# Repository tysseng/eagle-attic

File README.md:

# eagle-attic
Old eagle projects

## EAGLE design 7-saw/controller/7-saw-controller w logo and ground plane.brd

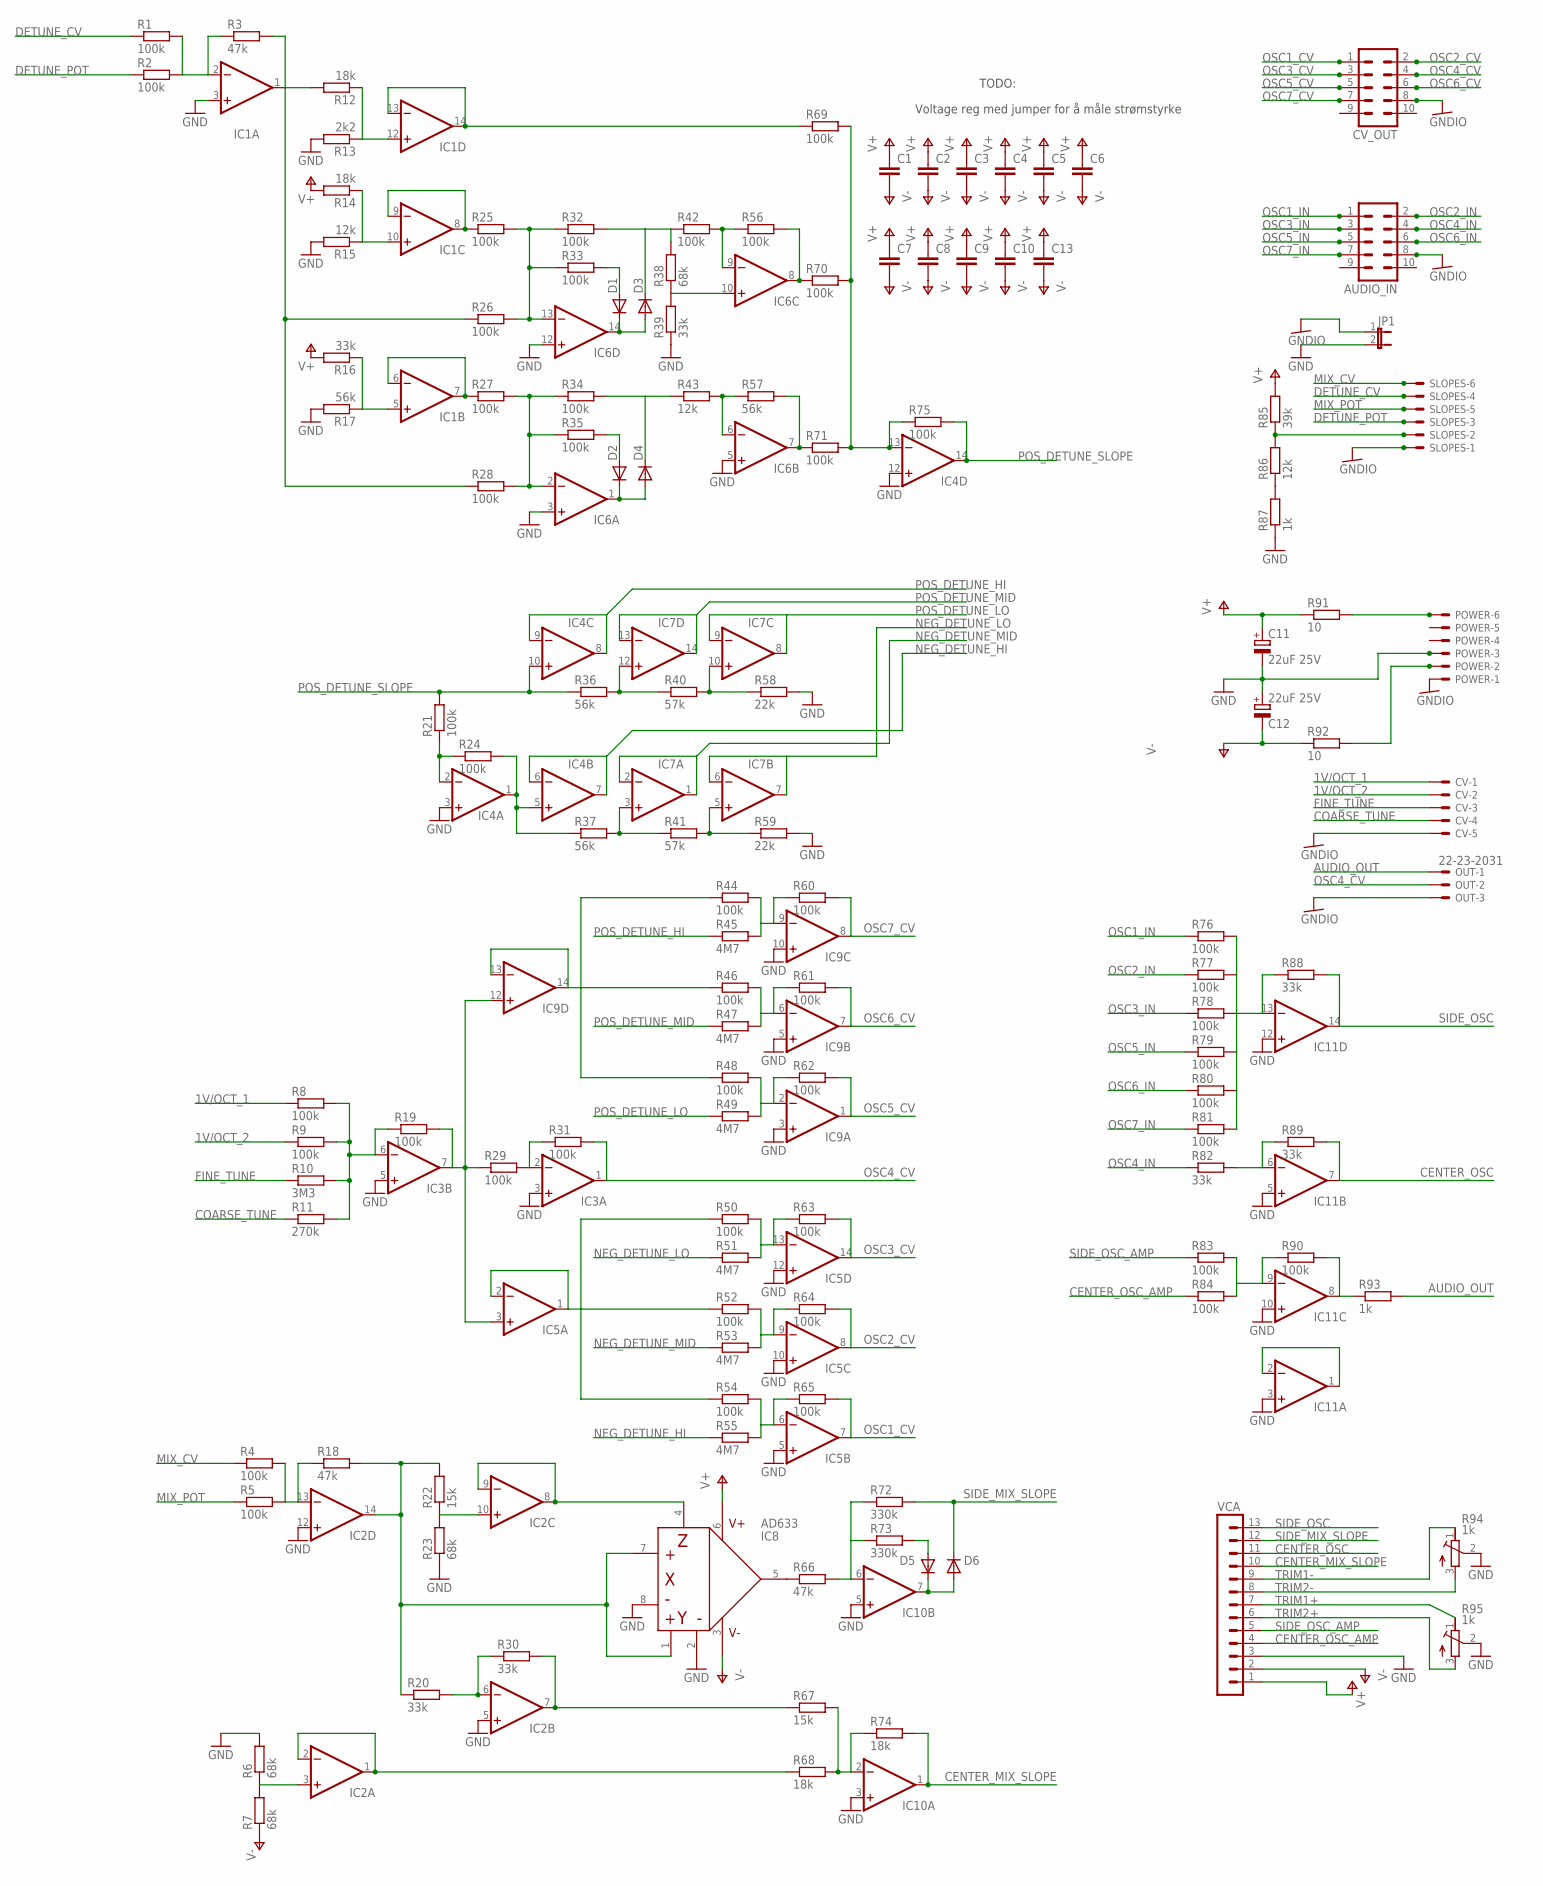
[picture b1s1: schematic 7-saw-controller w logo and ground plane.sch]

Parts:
AUDIO_IN: MA05-2
C1, C2, C3, C4, C5, C6, C7, C8, C9, C10, C13: C-EU025-024X044; C025-024X044
C11, C12: 22uF 25V; E2-5
CV: 22-23-2051
CV_OUT: MA05-2
D1, D2, D3, D4, D5, D6: DIODE-D-5; D-5
IC1, IC2, IC4, IC5, IC6, IC7, IC9, IC11: TL074D; SO14
IC3, IC10: TL072D; SO08
IC8: AD633; SO08
JP1: JP1E; JP1
OUT: 22-23-2031
POWER: 22-23-2061
R1, R2, R4, R5, R8, R9, R19, R21, R24, R25, R26, R27, R28, R29, R31, R32, R33, R34, R35, R42, R44, R46, R48, R50, R52, R54, R56, R60, R61, R62, R63, R64, R65, R69, R70, R71, R75, R76, R77, R78, R79, R80, R81, R83, R84, R90: 100k; 0204/5
R3, R18, R66: 47k; 0204/5
R6, R7, R23, R38: 68k; 0204/5
R10: 3M3; 0204/5
R11: 270k; 0204/5
R12, R14, R68, R74: 18k; 0204/5
R13: 2k2; 0204/5
R15, R43, R86: 12k; 0204/5
R16, R20, R30, R39, R82, R88, R89: 33k; 0204/5
R17, R36, R37, R57: 56k; 0204/5
R22, R67: 15k; 0204/5
R40, R41: 57k; 0204/5
R45, R47, R49, R51, R53, R55: 4M7; 0204/5
R58, R59: 22k; 0204/5
R72, R73: 330k; 0204/5
R85: 39k; 0204/5
R87, R93: 1k; 0204/5
R91, R92: 10; 0204/7
R94, R95: 1k; RTRIMT93YA
SLOPES: 22-23-2061
VCA: MA13-1

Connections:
1V/OCT_1: CV.1, R8.1
1V/OCT_2: CV.2, R9.1
AUDIO_OUT: OUT.1, R93.2
CENTER_MIX_SLOPE: IC10.1 (OUT), R74.2, VCA.10
CENTER_OSC: IC11.7 (OUT), R89.2, VCA.11
CENTER_OSC_AMP: R84.1, VCA.4
COARSE_TUNE: CV.4, R11.1
DETUNE_CV: R1.1, SLOPES.4
DETUNE_MIXED: R12.2, R26.1, R28.1
DETUNE_POT: R2.1, SLOPES.3
FINE_TUNE: CV.3, R10.1
GND: C11.-, C12.+, IC1.3 (+IN), IC2.5 (+IN), IC2.12 (+IN), IC3.3 (+IN), IC3.5 (+IN), IC4.3 (+IN), IC4.12 (+IN), IC5.5 (+IN), IC5.10 (+IN), IC5.12 (+IN), IC6.3 (+IN), IC6.5 (+IN), IC6.12 (+IN), IC8.2, IC8.8, IC9.3 (+IN), IC9.5 (+IN), IC9.10 (+IN), IC10.3 (+IN), IC10.5 (+IN), IC11.3 (+IN), IC11.5 (+IN), IC11.10 (+IN), IC11.12 (+IN), JP1.2, POWER.3, R6.2, R13.2, R15.2, R17.2, R23.1, R39.1, R58.2, R59.2, R87.1, R94.2 (S), R95.2 (S), VCA.3
GNDIO: AUDIO_IN.8, CV.5, CV_OUT.8, JP1.1, OUT.3, POWER.1, SLOPES.1
MIX_CV: R4.1, SLOPES.6
MIX_POT: R5.1, SLOPES.5
unnamed: IC1.12 (+IN), R12.1, R13.1
unnamed: IC1.13 (-IN), IC1.14 (OUT), R69.1
unnamed: IC1.10 (+IN), R14.1, R15.1
unnamed: IC1.8 (OUT), IC1.9 (-IN), R25.1
unnamed: IC6.13 (-IN), R25.2, R26.2, R32.1, R33.1
unnamed: IC6.7 (OUT), R57.2, R71.1
unnamed: IC10.2 (-IN), R67.2, R68.2, R74.1
unnamed: IC3.7 (OUT), IC5.3 (+IN), IC9.12 (+IN), R19.2, R29.1
unnamed: IC4.13 (-IN), R69.2, R70.2, R71.2, R75.1
unnamed: D1.A, R33.2
unnamed: D1.C, D3.A, IC6.14 (OUT)
unnamed: D3.C, R32.2, R38.2, R42.1
unnamed: IC2.14 (OUT), IC8.1, IC8.7, R18.2, R20.1, R22.2
unnamed: IC6.9 (-IN), R42.2, R56.1
unnamed: IC6.10 (+IN), R38.1, R39.2
unnamed: IC6.8 (OUT), R56.2, R70.1
unnamed: IC2.8 (OUT), IC2.9 (-IN), IC8.4
unnamed: IC1.5 (+IN), R16.1, R17.1
unnamed: IC1.6 (-IN), IC1.7 (OUT), R27.1
unnamed: IC2.10 (+IN), R22.1, R23.2
unnamed: IC6.2 (-IN), R27.2, R28.2, R34.1, R35.1
unnamed: D5.A, R73.2
unnamed: IC2.3 (+IN), R6.1, R7.2
unnamed: D2.A, R35.2
unnamed: D2.C, D4.A, IC6.1 (OUT)
unnamed: D4.C, R34.2, R43.1
unnamed: IC6.6 (-IN), R43.2, R57.1
unnamed: D5.C, D6.A, IC10.7 (OUT)
unnamed: IC2.1 (OUT), IC2.2 (-IN), R68.1
unnamed: IC2.6 (-IN), R20.2, R30.1
unnamed: IC2.7 (OUT), R30.2, R67.1
unnamed: IC9.9 (-IN), R44.2, R45.2, R60.1
unnamed: IC5.13 (-IN), R50.2, R51.2, R63.1
unnamed: IC5.9 (-IN), R52.2, R53.2, R64.1
unnamed: IC8.5, R66.1
unnamed: IC5.6 (-IN), R54.2, R55.2, R65.1
unnamed: IC10.6 (-IN), R66.2, R72.1, R73.1
unnamed: IC5.1 (OUT), IC5.2 (-IN), R50.1, R52.1, R54.1
unnamed: IC9.6 (-IN), R46.2, R47.2, R61.1
unnamed: POWER.6, R91.2
unnamed: IC9.13 (-IN), IC9.14 (OUT), R44.1, R46.1, R48.1
unnamed: R85.1, R86.2, SLOPES.2
unnamed: IC9.2 (-IN), R48.2, R49.2, R62.1
unnamed: POWER.2, R92.2
unnamed: IC3.6 (-IN), R8.2, R9.2, R10.2, R11.2, R19.1
unnamed: IC11.13 (-IN), R76.2, R77.2, R78.2, R79.2, R80.2, R81.2, R88.1
unnamed: IC11.6 (-IN), R82.2, R89.1
unnamed: IC11.9 (-IN), R83.2, R84.2, R90.1
unnamed: IC1.1 (OUT), R3.2
unnamed: IC11.8 (OUT), R90.2, R93.1
unnamed: IC2.13 (-IN), R4.2, R5.2, R18.1
unnamed: IC7.12 (+IN), R36.2, R40.1
unnamed: IC7.10 (+IN), R40.2, R58.1
unnamed: IC4.1 (OUT), IC4.5 (+IN), R24.2, R37.1
unnamed: IC1.2 (-IN), R1.2, R2.2, R3.1
unnamed: IC3.2 (-IN), R29.2, R31.1
unnamed: IC7.3 (+IN), R37.2, R41.1
unnamed: IC7.5 (+IN), R41.2, R59.1
unnamed: R86.1, R87.2
unnamed: IC4.2 (-IN), R21.1, R24.1
unnamed: IC11.1 (OUT), IC11.2 (-IN)
NEG_DETUNE_HI: IC4.6 (-IN), IC4.7 (OUT), R55.1
NEG_DETUNE_LO: IC7.6 (-IN), IC7.7 (OUT), R51.1
NEG_DETUNE_MID: IC7.1 (OUT), IC7.2 (-IN), R53.1
OSC1_CV: CV_OUT.1, IC5.7 (OUT), R65.2
OSC1_IN: AUDIO_IN.1, R76.1
OSC2_CV: CV_OUT.2, IC5.8 (OUT), R64.2
OSC2_IN: AUDIO_IN.2, R77.1
OSC3_CV: CV_OUT.3, IC5.14 (OUT), R63.2
OSC3_IN: AUDIO_IN.3, R78.1
OSC4_CV: CV_OUT.4, IC3.1 (OUT), OUT.2, R31.2
OSC4_IN: AUDIO_IN.4, R82.1
OSC5_CV: CV_OUT.5, IC9.1 (OUT), R62.2
OSC5_IN: AUDIO_IN.5, R79.1
OSC6_CV: CV_OUT.6, IC9.7 (OUT), R61.2
OSC6_IN: AUDIO_IN.6, R80.1
OSC7_CV: CV_OUT.7, IC9.8 (OUT), R60.2
OSC7_IN: AUDIO_IN.7, R81.1
POS_DETUNE_HI: IC4.8 (OUT), IC4.9 (-IN), R45.1
POS_DETUNE_LO: IC7.8 (OUT), IC7.9 (-IN), R49.1
POS_DETUNE_MID: IC7.13 (-IN), IC7.14 (OUT), R47.1
POS_DETUNE_SLOPE: IC4.10 (+IN), IC4.14 (OUT), R21.2, R36.1, R75.2
SIDE_MIX_SLOPE: D6.C, R72.2, VCA.12
SIDE_OSC: IC11.14 (OUT), R88.2, VCA.13
SIDE_OSC_AMP: R83.1, VCA.5
TRIM1+: R94.3 (E), VCA.8
TRIM1-: R94.1 (A), VCA.9
TRIM2+: R95.3 (E), VCA.6
TRIM2-: R95.1 (A), VCA.7
V+: C1.1, C2.1, C3.1, C4.1, C5.1, C6.1, C7.1, C8.1, C9.1, C10.1, C11.+, C13.1, IC1.4 (V+), IC2.4 (V+), IC3.8 (V+), IC4.4 (V+), IC5.4 (V+), IC6.4 (V+), IC7.4 (V+), IC8.6, IC9.4 (V+), IC10.8 (V+), IC11.4 (V+), R14.2, R16.2, R85.2, R91.1, VCA.1
V-: C1.2, C2.2, C3.2, C4.2, C5.2, C6.2, C7.2, C8.2, C9.2, C10.2, C12.-, C13.2, IC1.11 (V-), IC2.11 (V-), IC3.4 (V-), IC4.11 (V-), IC5.11 (V-), IC6.11 (V-), IC7.11 (V-), IC8.3, IC9.11 (V-), IC10.4 (V-), IC11.11 (V-), R7.1, R92.1, VCA.2

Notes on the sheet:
TODO:
Voltage reg med jumper for å måle strømstyrke

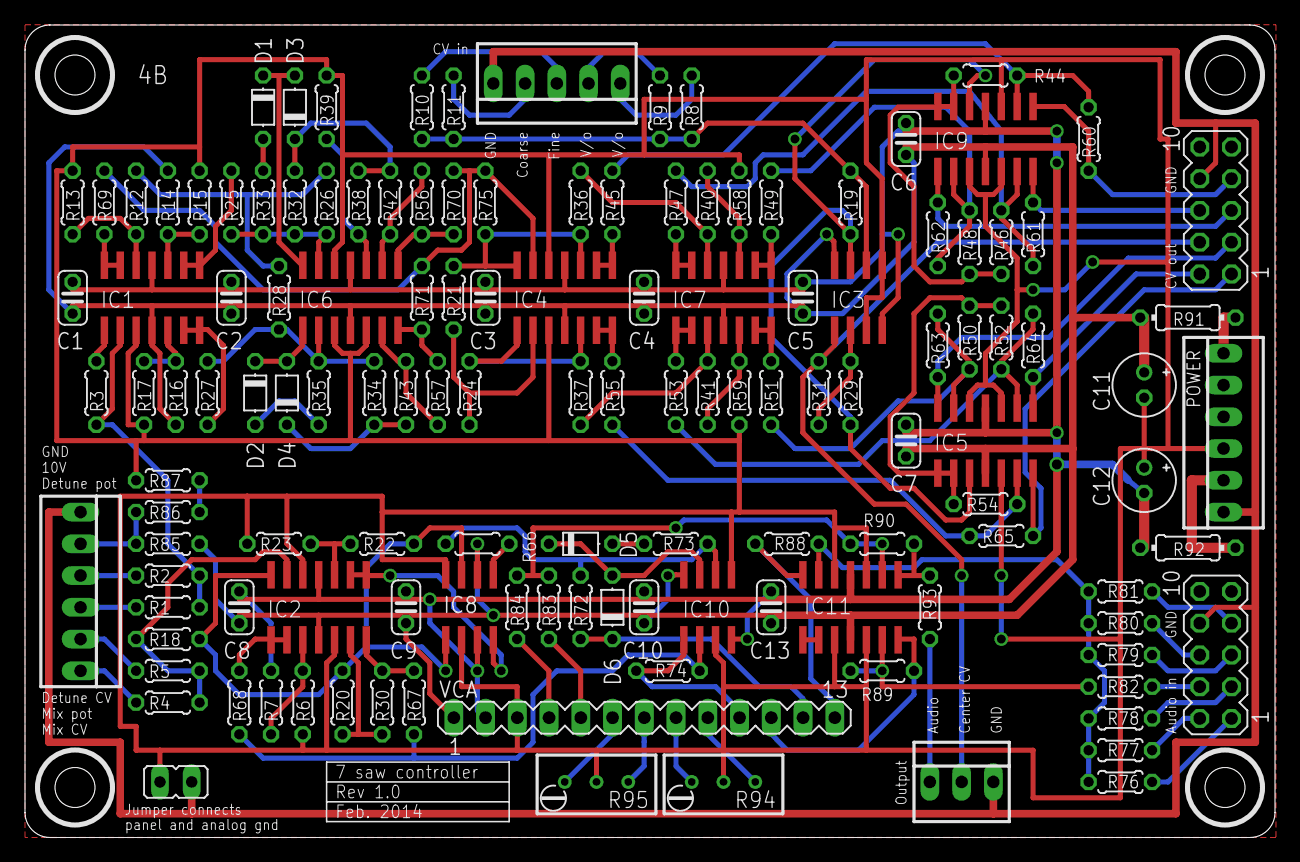
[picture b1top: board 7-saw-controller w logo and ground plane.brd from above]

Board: 2 copper layers, 100.0 x 65.0 mm, 133 parts (0 on the bottom side), 106 nets.

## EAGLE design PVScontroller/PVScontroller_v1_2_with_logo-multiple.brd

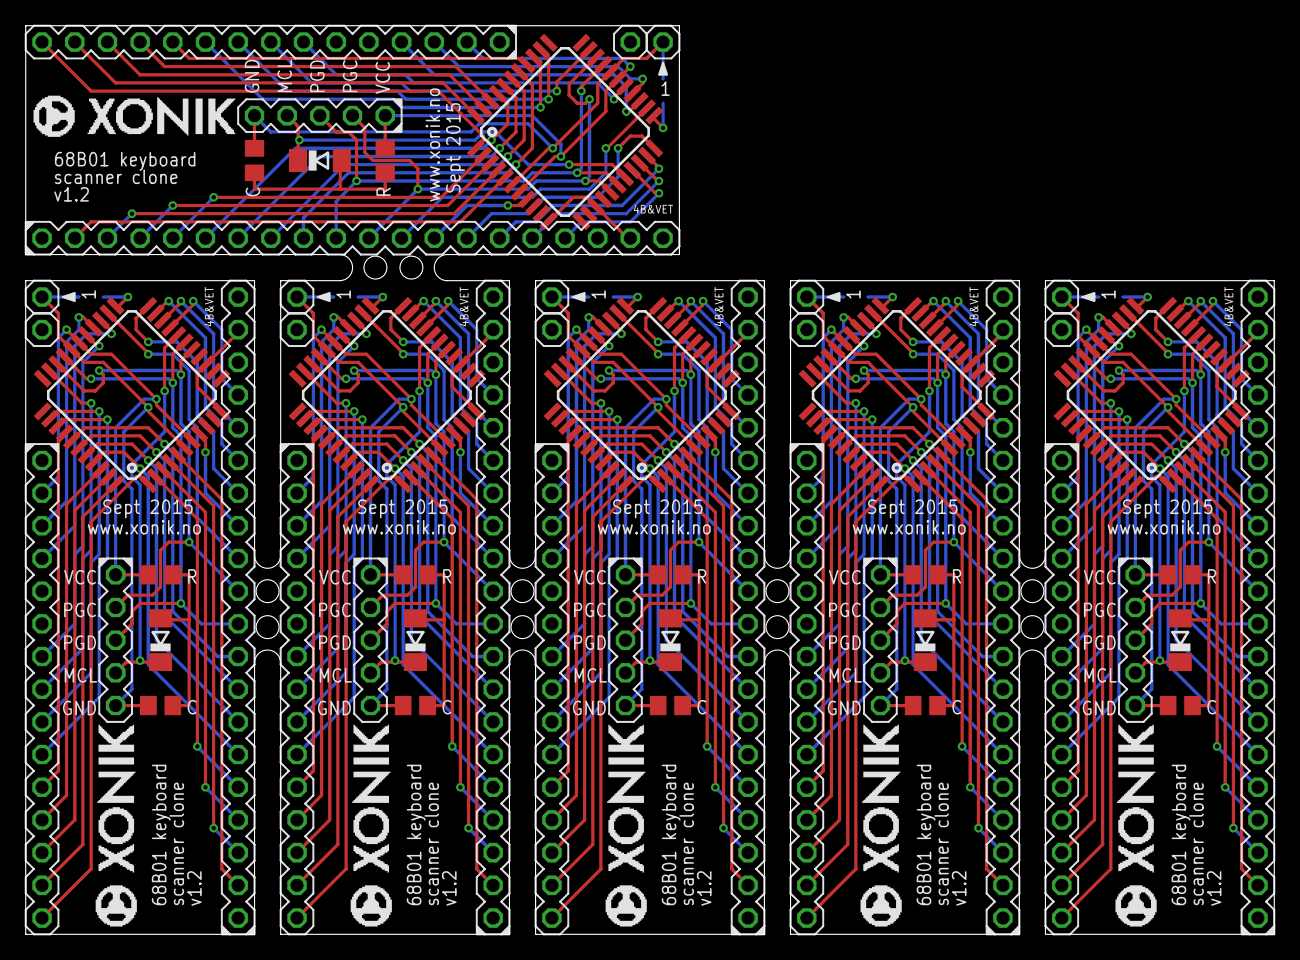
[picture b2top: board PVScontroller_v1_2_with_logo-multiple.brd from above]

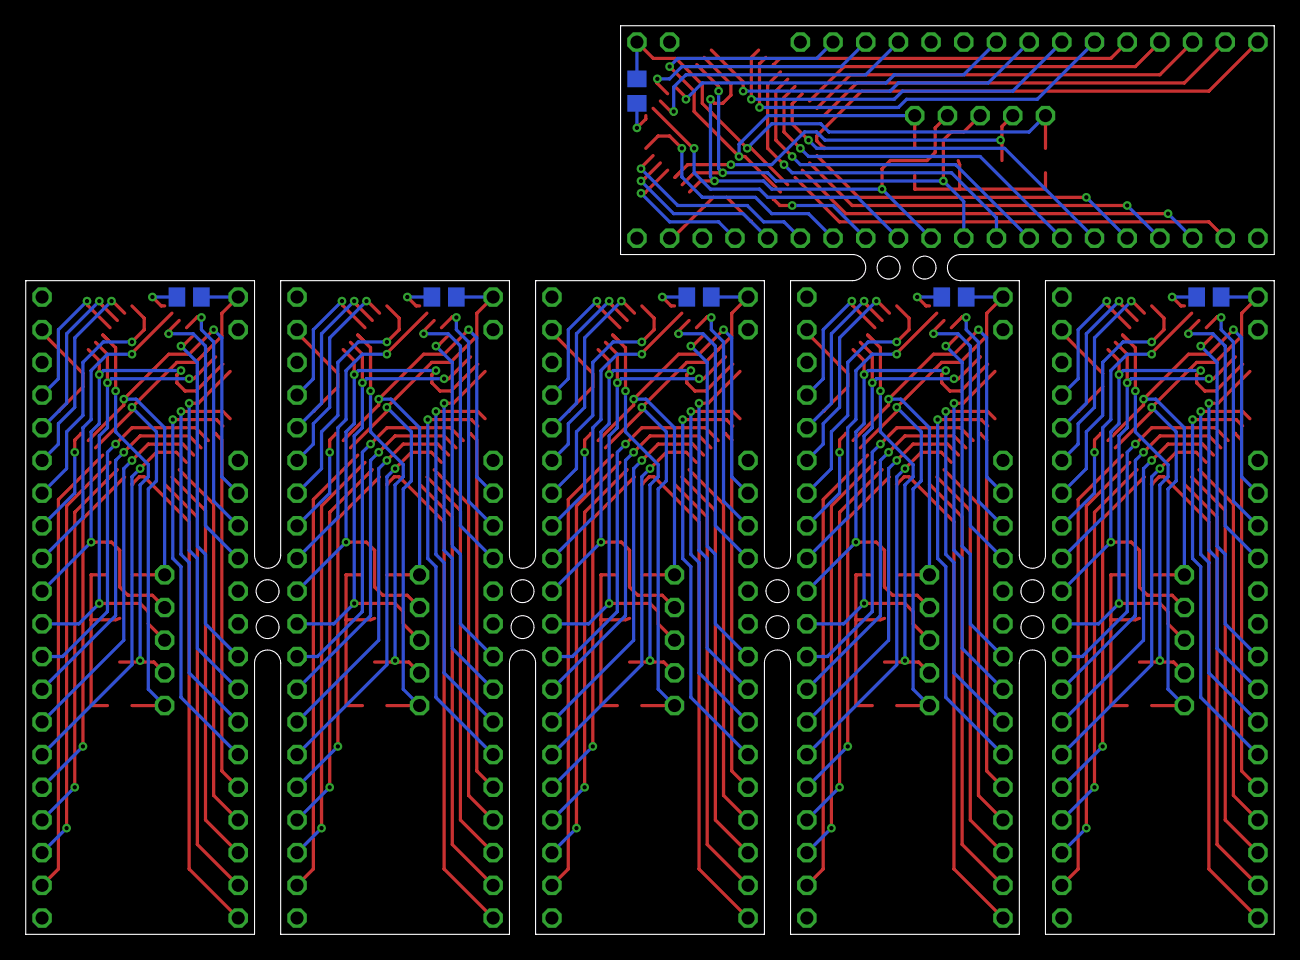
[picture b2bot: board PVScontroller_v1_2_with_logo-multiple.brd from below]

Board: 2 copper layers, 97.0 x 70.6 mm, 60 parts (6 on the bottom side), 198 nets.

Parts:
C, C1, C4, C6, C8, C10: 100nF; C0805
C2, C3, C5, C7, C9, C11: 10uF; C0805
D1, D2, D3, D4, D5, D6: SOD80C
IC1, IC2, IC3, IC4, IC5, IC6: PIC18F4455_TQFP; TQFP44
R, R1, R2, R3, R4, R5: 10k; R0805
SV1, SV3, SV5, SV8, SV11, SV13, SV16, SV18, SV21, SV23, SV26, SV28: MA01-1
SV2, SV10, SV15, SV20, SV25, SV30: MA20-1
SV4, SV7, SV12, SV17, SV22, SV27: MA05-1
SV6, SV9, SV14, SV19, SV24, SV29: MA15-1

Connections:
+5V: IC1.7, IC1.28, R.2, SV7.1, SV9.2
+5V1: IC2.7, IC2.28, R1.2, SV4.1, SV6.2
+5V2: IC3.7, IC3.28, R2.2, SV12.1, SV14.2
+5V3: IC4.7, IC4.28, R3.2, SV17.1, SV19.2
+5V4: IC5.7, IC5.28, R4.2, SV22.1, SV24.2
+5V5: IC6.7, IC6.28, R5.2, SV27.1, SV29.2
BS0: IC1.19, SV2.17
BS1: IC1.20, SV2.16
BS2: IC1.21, SV2.15
BS3: IC1.22, SV2.14
BS4: IC1.8, SV2.13
BS5: IC1.24, SV2.12
BS6: IC1.16, IC1.31, SV2.11, SV7.2
BS7: IC1.17, IC1.30, SV2.10, SV7.3
BS8: IC2.19, SV10.17
BS9: IC2.20, SV10.16
BS10: IC2.21, SV10.15
BS11: IC2.22, SV10.14
BS12: IC2.8, SV10.13
BS13: IC2.24, SV10.12
BS14: IC2.16, IC2.31, SV4.2, SV10.11
BS15: IC2.17, IC2.30, SV4.3, SV10.10
BS16: IC3.19, SV15.17
BS17: IC3.20, SV15.16
BS18: IC3.21, SV15.15
BS19: IC3.22, SV15.14
BS20: IC3.8, SV15.13
BS21: IC3.24, SV15.12
BS22: IC3.16, IC3.31, SV12.2, SV15.11
BS23: IC3.17, IC3.30, SV12.3, SV15.10
BS24: IC4.19, SV20.17
BS25: IC4.20, SV20.16
BS26: IC4.21, SV20.15
BS27: IC4.22, SV20.14
BS28: IC4.8, SV20.13
BS29: IC4.24, SV20.12
BS30: IC4.16, IC4.31, SV17.2, SV20.11
BS31: IC4.17, IC4.30, SV17.3, SV20.10
BS32: IC5.19, SV25.17
BS33: IC5.20, SV25.16
BS34: IC5.21, SV25.15
BS35: IC5.22, SV25.14
BS36: IC5.8, SV25.13
BS37: IC5.24, SV25.12
BS38: IC5.16, IC5.31, SV22.2, SV25.11
BS39: IC5.17, IC5.30, SV22.3, SV25.10
BS40: IC6.19, SV30.17
BS41: IC6.20, SV30.16
BS42: IC6.21, SV30.15
BS43: IC6.22, SV30.14
BS44: IC6.8, SV30.13
BS45: IC6.24, SV30.12
BS46: IC6.16, IC6.31, SV27.2, SV30.11
BS47: IC6.17, IC6.30, SV27.3, SV30.10
CARRY: IC1.25, SV9.4
CARRY1: IC2.25, SV6.4
CARRY2: IC3.25, SV14.4
CARRY3: IC4.25, SV19.4
CARRY4: IC5.25, SV24.4
CARRY5: IC6.25, SV29.4
CLK: IC1.26, SV9.3
CLK1: IC2.26, SV6.3
CLK2: IC3.26, SV14.3
CLK3: IC4.26, SV19.3
CLK4: IC5.26, SV24.3
CLK5: IC6.26, SV29.3
DB0: IC1.38, SV2.9
DB1: IC1.39, SV2.8
DB2: IC1.40, SV2.7
DB3: IC1.41, SV2.6
DB4: IC1.2, SV2.5
DB5: IC1.3, SV2.4
DB6: IC1.4, SV2.3
DB7: IC1.5, SV2.2
DB8: IC2.38, SV10.9
DB9: IC2.39, SV10.8
DB10: IC2.40, SV10.7
DB11: IC2.41, SV10.6
DB12: IC2.2, SV10.5
DB13: IC2.3, SV10.4
DB14: IC2.4, SV10.3
DB15: IC2.5, SV10.2
DB16: IC3.38, SV15.9
DB17: IC3.39, SV15.8
DB18: IC3.40, SV15.7
DB19: IC3.41, SV15.6
DB20: IC3.2, SV15.5
DB21: IC3.3, SV15.4
DB22: IC3.4, SV15.3
DB23: IC3.5, SV15.2
DB24: IC4.38, SV20.9
DB25: IC4.39, SV20.8
DB26: IC4.40, SV20.7
DB27: IC4.41, SV20.6
DB28: IC4.2, SV20.5
DB29: IC4.3, SV20.4
DB30: IC4.4, SV20.3
DB31: IC4.5, SV20.2
DB32: IC5.38, SV25.9
DB33: IC5.39, SV25.8
DB34: IC5.40, SV25.7
DB35: IC5.41, SV25.6
DB36: IC5.2, SV25.5
DB37: IC5.3, SV25.4
DB38: IC5.4, SV25.3
DB39: IC5.5, SV25.2
DB40: IC6.38, SV30.9
DB41: IC6.39, SV30.8
DB42: IC6.40, SV30.7
DB43: IC6.41, SV30.6
DB44: IC6.2, SV30.5
DB45: IC6.3, SV30.4
DB46: IC6.4, SV30.3
DB47: IC6.5, SV30.2
GND: C.1, C2.1, IC1.6, IC1.29, SV1.1, SV7.5
GND1: C1.1, C3.1, IC2.6, IC2.29, SV3.1, SV4.5
GND2: C4.1, C5.1, IC3.6, IC3.29, SV11.1, SV12.5
GND3: C6.1, C7.1, IC4.6, IC4.29, SV16.1, SV17.5
GND4: C8.1, C9.1, IC5.6, IC5.29, SV21.1, SV22.5
GND5: C10.1, C11.1, IC6.6, IC6.29, SV26.1, SV27.5
KYBD: IC1.11, IC1.14, SV2.19
KYBD1: IC2.11, IC2.14, SV10.19
KYBD2: IC3.11, IC3.14, SV15.19
KYBD3: IC4.11, IC4.14, SV20.19
KYBD4: IC5.11, IC5.14, SV25.19
KYBD5: IC6.11, IC6.14, SV30.19
KYINT: IC1.27, SV9.7
KYINT1: IC2.27, SV6.7
KYINT2: IC3.27, SV14.7
KYINT3: IC4.27, SV19.7
KYINT4: IC5.27, SV24.7
KYINT5: IC6.27, SV29.7
MCLR: D1.C, IC1.18, SV7.4
MCLR1: D2.C, IC2.18, SV4.4
MCLR2: D3.C, IC3.18, SV12.4
MCLR3: D4.C, IC4.18, SV17.4
MCLR4: D5.C, IC5.18, SV22.4
MCLR5: D6.C, IC6.18, SV27.4
unnamed: C1.2, D2.A, R1.1
unnamed: C4.2, D3.A, R2.1
unnamed: C6.2, D4.A, R3.1
unnamed: C.2, D1.A, R.1
unnamed: C8.2, D5.A, R4.1
unnamed: C10.2, D6.A, R5.1
TS0: IC1.32, SV9.8
TS1: IC1.35, SV9.9
TS2: IC1.36, SV9.10
TS3: IC1.37, SV9.11
TS4: IC1.42, SV9.12
TS5: IC1.43, SV9.13
TS6: IC1.44, SV9.14
TS7: IC1.1, SV9.15
TS8: IC2.32, SV6.8
TS9: IC2.35, SV6.9
TS10: IC2.36, SV6.10
TS11: IC2.37, SV6.11
TS12: IC2.42, SV6.12
TS13: IC2.43, SV6.13
TS14: IC2.44, SV6.14
TS15: IC2.1, SV6.15
TS16: IC3.32, SV14.8
TS17: IC3.35, SV14.9
TS18: IC3.36, SV14.10
TS19: IC3.37, SV14.11
TS20: IC3.42, SV14.12
TS21: IC3.43, SV14.13
TS22: IC3.44, SV14.14
TS23: IC3.1, SV14.15
TS24: IC4.32, SV19.8
TS25: IC4.35, SV19.9
TS26: IC4.36, SV19.10
TS27: IC4.37, SV19.11
TS28: IC4.42, SV19.12
TS29: IC4.43, SV19.13
TS30: IC4.44, SV19.14
TS31: IC4.1, SV19.15
TS32: IC5.32, SV24.8
TS33: IC5.35, SV24.9
TS34: IC5.36, SV24.10
TS35: IC5.37, SV24.11
TS36: IC5.42, SV24.12
TS37: IC5.43, SV24.13
TS38: IC5.44, SV24.14
TS39: IC5.1, SV24.15
TS40: IC6.32, SV29.8
TS41: IC6.35, SV29.9
TS42: IC6.36, SV29.10
TS43: IC6.37, SV29.11
TS44: IC6.42, SV29.12
TS45: IC6.43, SV29.13
TS46: IC6.44, SV29.14
TS47: IC6.1, SV29.15
VDD_CORE: C2.2, IC1.23
VDD_CORE1: C3.2, IC2.23
VDD_CORE2: C5.2, IC3.23
VDD_CORE3: C7.2, IC4.23
VDD_CORE4: C9.2, IC5.23
VDD_CORE5: C11.2, IC6.23

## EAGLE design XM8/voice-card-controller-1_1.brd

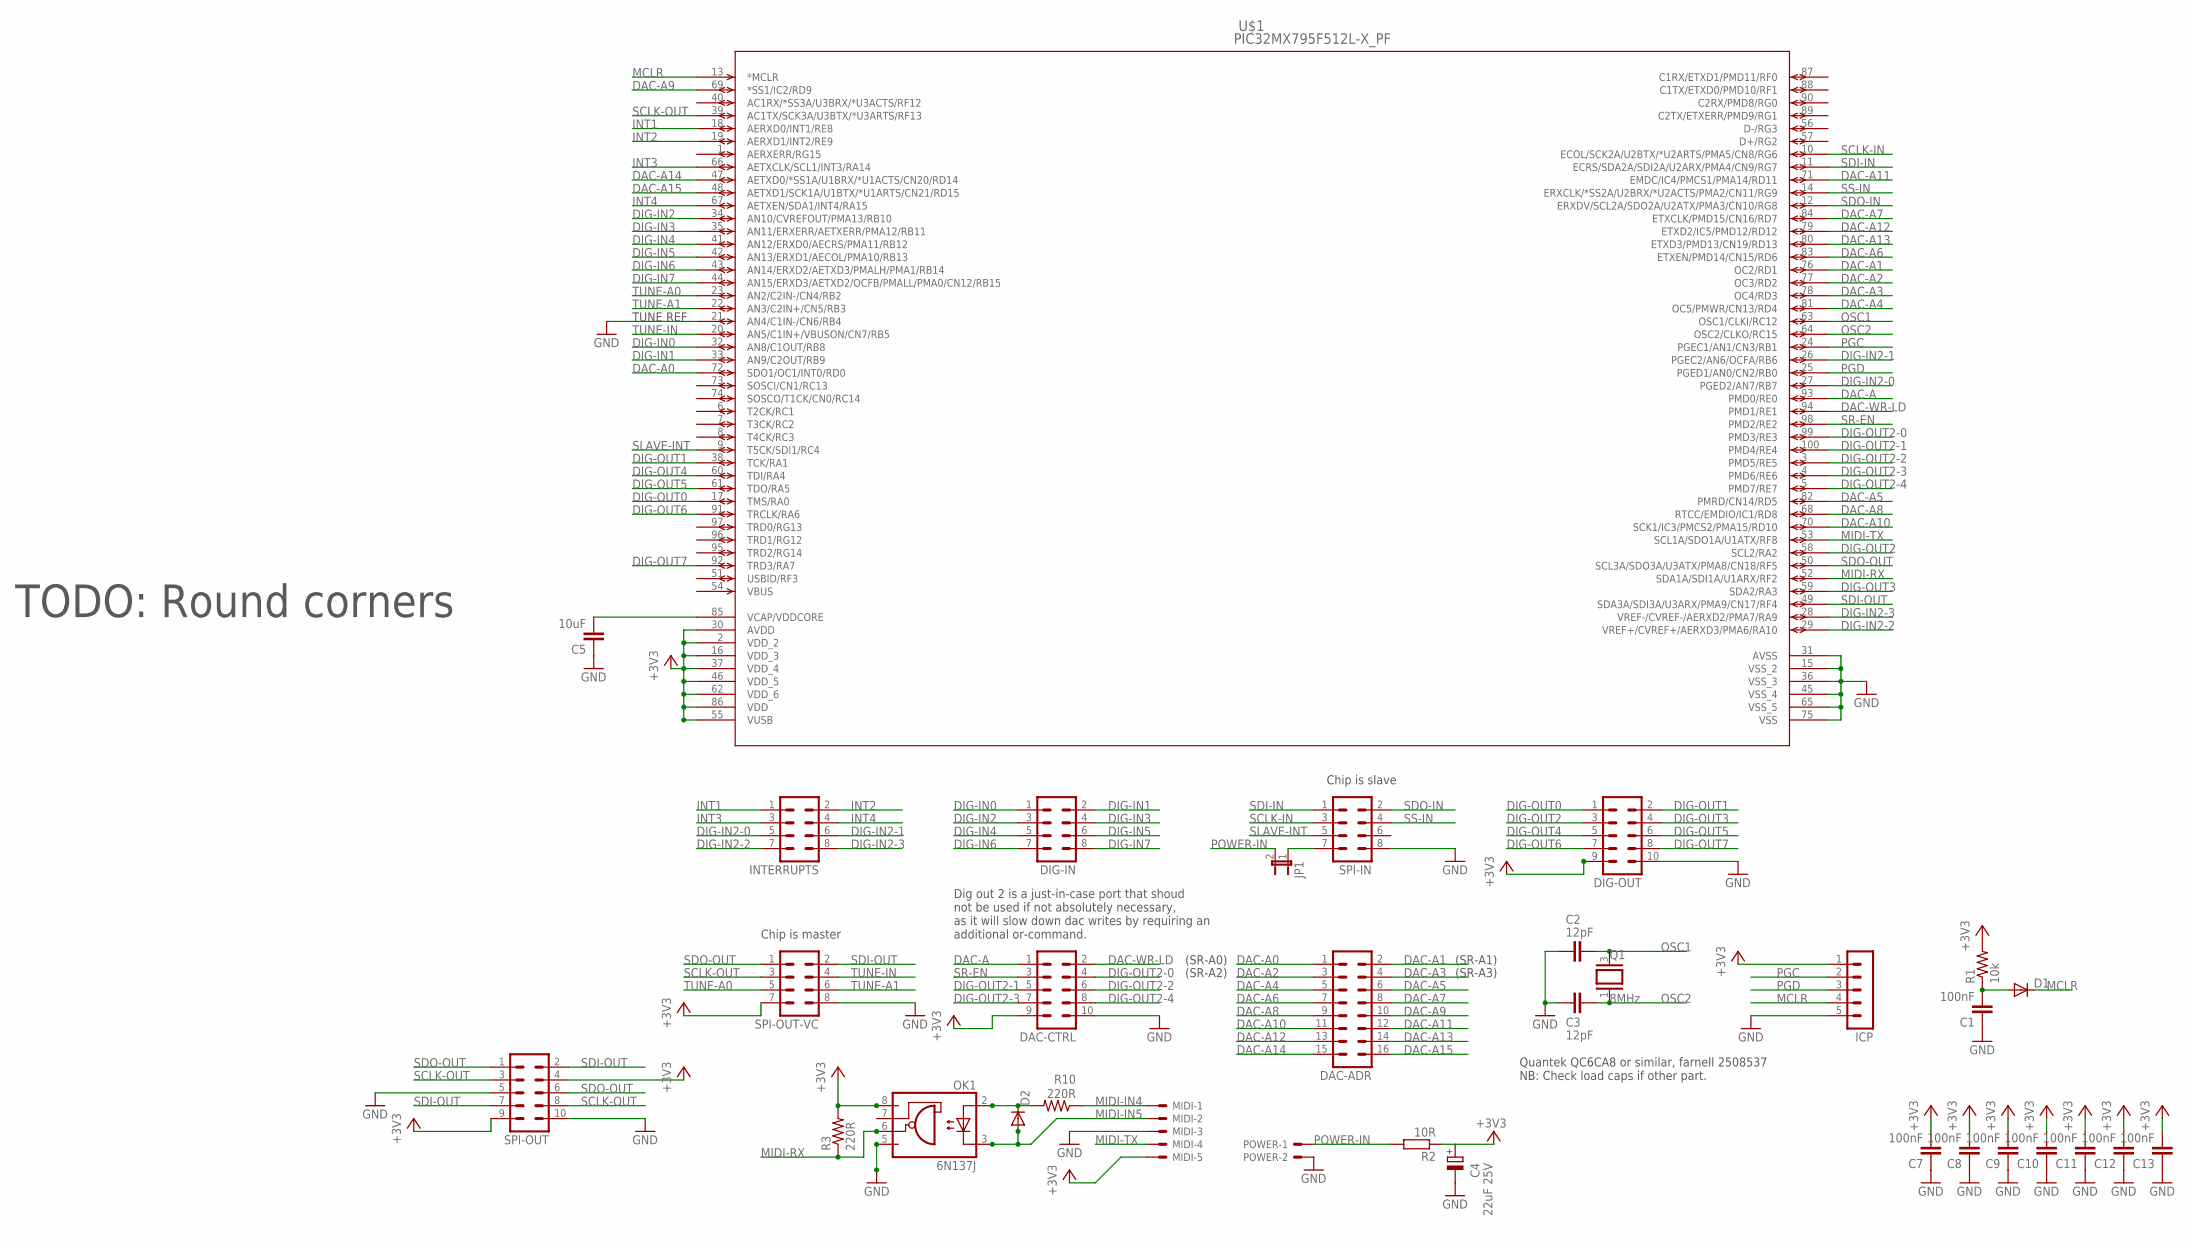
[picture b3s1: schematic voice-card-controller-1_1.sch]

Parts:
C1, C7, C8, C9, C10, C11, C12, C13: 100nF; C0603
C2, C3: 12pF; C0603
C4: 22uF 25V; E2,5-5
C5: 10uF; C0805
D1, D2: DIODE-SOD80C; SOD80C
DAC-ADR: MA08-2J
DAC-CTRL: MA05-2J
DIG-IN: MA04-2J
DIG-OUT: MA05-2J
ICP: MA05-1
INTERRUPTS: MA04-2J
JP1: JP1E; JP1
MIDI: 22-23-2051
OK1: 6N137J; DIL08-J
POWER: 22-23-2021
Q1: 8MHz; CTS406J
R1: 10k; R0805
R2: 10R; 0207/7
R3, R10: 220R; R0805
SPI-IN: MA04-2J
SPI-OUT: MA05-2J
SPI-OUT-VC: MA04-2J
U$1: PIC32MX795F512L-X_PF; TQFP100_14X14MC

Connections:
+3V3: C4.+, C7.2, C8.2, C9.2, C10.2, C11.2, C12.2, C13.2, DAC-CTRL.9, DIG-OUT.9, ICP.1, MIDI.5, OK1.8 (VCC), R1.2, R2.1, R3.2, SPI-OUT.4, SPI-OUT.9, SPI-OUT-VC.7, U$1.2 (VDD_2), U$1.16 (VDD_3), U$1.30 (AVDD), U$1.37 (VDD_4), U$1.46 (VDD_5), U$1.55 (VUSB), U$1.62 (VDD_6), U$1.86 (VDD)
DAC-A: DAC-CTRL.1, U$1.93 (PMD0/RE0)
DAC-A0: DAC-ADR.1, U$1.72 (SDO1/OC1/INT0/RD0)
DAC-A1: DAC-ADR.2, U$1.76 (OC2/RD1)
DAC-A2: DAC-ADR.3, U$1.77 (OC3/RD2)
DAC-A3: DAC-ADR.4, U$1.78 (OC4/RD3)
DAC-A4: DAC-ADR.5, U$1.81 (OC5/PMWR/CN13/RD4)
DAC-A5: DAC-ADR.6, U$1.82 (PMRD/CN14/RD5)
DAC-A6: DAC-ADR.7, U$1.83 (ETXEN/PMD14/CN15/RD6)
DAC-A7: DAC-ADR.8, U$1.84 (ETXCLK/PMD15/CN16/RD7)
DAC-A8: DAC-ADR.9, U$1.68 (RTCC/EMDIO/IC1/RD8)
DAC-A9: DAC-ADR.10, U$1.69 (*SS1/IC2/RD9)
DAC-A10: DAC-ADR.11, U$1.70 (SCK1/IC3/PMCS2/PMA15/RD10)
DAC-A11: DAC-ADR.12, U$1.71 (EMDC/IC4/PMCS1/PMA14/RD11)
DAC-A12: DAC-ADR.13, U$1.79 (ETXD2/IC5/PMD12/RD12)
DAC-A13: DAC-ADR.14, U$1.80 (ETXD3/PMD13/CN19/RD13)
DAC-A14: DAC-ADR.15, U$1.47 (AETXD0/*SS1A/U1BRX/*U1ACTS/CN20/RD14)
DAC-A15: DAC-ADR.16, U$1.48 (AETXD1/SCK1A/U1BTX/*U1ARTS/CN21/RD15)
DAC-WR-LD: DAC-CTRL.2, U$1.94 (PMD1/RE1)
DIG-IN0: DIG-IN.1, U$1.32 (AN8/C1OUT/RB8)
DIG-IN1: DIG-IN.2, U$1.33 (AN9/C2OUT/RB9)
DIG-IN2: DIG-IN.3, U$1.34 (AN10/CVREFOUT/PMA13/RB10)
DIG-IN2-0: INTERRUPTS.5, U$1.27 (PGED2/AN7/RB7)
DIG-IN2-1: INTERRUPTS.6, U$1.26 (PGEC2/AN6/OCFA/RB6)
DIG-IN2-2: INTERRUPTS.7, U$1.29 (VREF+/CVREF+/AERXD3/PMA6/RA10)
DIG-IN2-3: INTERRUPTS.8, U$1.28 (VREF-/CVREF-/AERXD2/PMA7/RA9)
DIG-IN3: DIG-IN.4, U$1.35 (AN11/ERXERR/AETXERR/PMA12/RB11)
DIG-IN4: DIG-IN.5, U$1.41 (AN12/ERXD0/AECRS/PMA11/RB12)
DIG-IN5: DIG-IN.6, U$1.42 (AN13/ERXD1/AECOL/PMA10/RB13)
DIG-IN6: DIG-IN.7, U$1.43 (AN14/ERXD2/AETXD3/PMALH/PMA1/RB14)
DIG-IN7: DIG-IN.8, U$1.44 (AN15/ERXD3/AETXD2/OCFB/PMALL/PMA0/CN12/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)
DIG-OUT0: DIG-OUT.1, U$1.17 (TMS/RA0)
DIG-OUT1: DIG-OUT.2, U$1.38 (TCK/RA1)
DIG-OUT2: DIG-OUT.3, U$1.58 (SCL2/RA2)
DIG-OUT2-0: DAC-CTRL.4, U$1.99 (PMD3/RE3)
DIG-OUT2-1: DAC-CTRL.5, U$1.100 (PMD4/RE4)
DIG-OUT2-2: DAC-CTRL.6, U$1.3 (PMD5/RE5)
DIG-OUT2-3: DAC-CTRL.7, U$1.4 (PMD6/RE6)
DIG-OUT2-4: DAC-CTRL.8, U$1.5 (PMD7/RE7)
DIG-OUT3: DIG-OUT.4, U$1.59 (SDA2/RA3)
DIG-OUT4: DIG-OUT.5, U$1.60 (TDI/RA4)
DIG-OUT5: DIG-OUT.6, U$1.61 (TDO/RA5)
DIG-OUT6: DIG-OUT.7, U$1.91 (TRCLK/RA6)
DIG-OUT7: DIG-OUT.8, U$1.92 (TRD3/RA7)
GND: C1.1, C2.2, C3.2, C4.-, C5.1, C7.1, C8.1, C9.1, C10.1, C11.1, C12.1, C13.1, DAC-CTRL.10, DIG-OUT.10, ICP.5, MIDI.3, OK1.5 (GND), POWER.2, SPI-IN.8, SPI-OUT.5, SPI-OUT.10, SPI-OUT-VC.8, U$1.15 (VSS_2), U$1.21 (AN4/C1IN-/CN6/RB4), U$1.31 (AVSS), U$1.36 (VSS_3), U$1.45 (VSS_4), U$1.65 (VSS_5), U$1.75 (VSS)
INT1: INTERRUPTS.1, U$1.18 (AERXD0/INT1/RE8)
INT2: INTERRUPTS.2, U$1.19 (AERXD1/INT2/RE9)
INT3: INTERRUPTS.3, U$1.66 (AETXCLK/SCL1/INT3/RA14)
INT4: INTERRUPTS.4, U$1.67 (AETXEN/SDA1/INT4/RA15)
MCLR: D1.C, ICP.4, U$1.13 (*MCLR)
MIDI-IN4: MIDI.1, R10.1
MIDI-IN5: D2.A, MIDI.2, OK1.3 (C)
MIDI-RX: OK1.6 (VO), R3.1, U$1.52 (SDA1A/SDI1A/U1ARX/RF2)
MIDI-TX: MIDI.4, U$1.53 (SCL1A/SDO1A/U1ATX/RF8)
unnamed: C5.2, U$1.85 (VCAP/VDDCORE)
unnamed: JP1.1, SPI-IN.7
unnamed: C1.2, D1.A, R1.1
unnamed: D2.C, OK1.2 (A), R10.2
OSC1: C2.1, Q1.3 (2), U$1.63 (OSC1/CLKI/RC12)
OSC2: C3.1, Q1.1, U$1.64 (OSC2/CLKO/RC15)
PGC: ICP.2, U$1.24 (PGEC1/AN1/CN3/RB1)
PGD: ICP.3, U$1.25 (PGED1/AN0/CN2/RB0)
POWER-IN: JP1.2, POWER.1, R2.2
SCLK-IN: SPI-IN.3, U$1.10 (ECOL/SCK2A/U2BTX/*U2ARTS/PMA5/CN8/RG6)
SCLK-OUT: SPI-OUT.3, SPI-OUT.8, SPI-OUT-VC.3, U$1.39 (AC1TX/SCK3A/U3BTX/*U3ARTS/RF13)
SDI-IN: SPI-IN.1, U$1.11 (ECRS/SDA2A/SDI2A/U2ARX/PMA4/CN9/RG7)
SDI-OUT: SPI-OUT.2, SPI-OUT.7, SPI-OUT-VC.2, U$1.49 (SDA3A/SDI3A/U3ARX/PMA9/CN17/RF4)
SDO-IN: SPI-IN.2, U$1.12 (ERXDV/SCL2A/SDO2A/U2ATX/PMA3/CN10/RG8)
SDO-OUT: SPI-OUT.1, SPI-OUT.6, SPI-OUT-VC.1, U$1.50 (SCL3A/SDO3A/U3ATX/PMA8/CN18/RF5)
SLAVE-INT: SPI-IN.5, U$1.9 (T5CK/SDI1/RC4)
SR-EN: DAC-CTRL.3, U$1.98 (PMD2/RE2)
SS-IN: SPI-IN.4, U$1.14 (ERXCLK/*SS2A/U2BRX/*U2ACTS/PMA2/CN11/RG9)
TUNE-A0: SPI-OUT-VC.5, U$1.23 (AN2/C2IN-/CN4/RB2)
TUNE-A1: SPI-OUT-VC.6, U$1.22 (AN3/C2IN+/CN5/RB3)
TUNE-IN: SPI-OUT-VC.4, U$1.20 (AN5/C1IN+/VBUSON/CN7/RB5)

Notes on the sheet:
(SR-A0)
(SR-A2)
(SR-A1)
(SR-A3)
Chip is slave
Chip is master
TUNE REF
Dig out 2 is a just-in-case port that shoud not be used if not absolutely necessary, as it will slow down dac writes by requiring an additional or-command.
Quantek QC6CA8 or similar, farnell 2508537 NB: Check load caps if other part.
TODO: Round corners

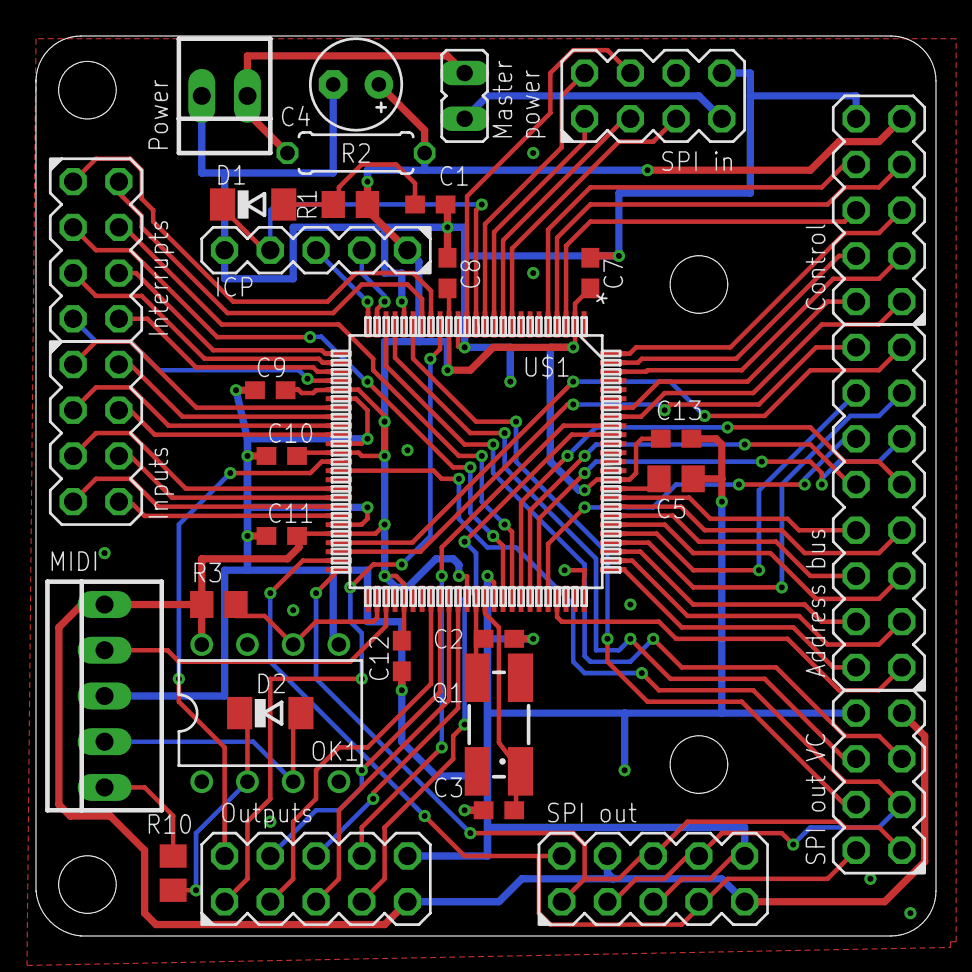
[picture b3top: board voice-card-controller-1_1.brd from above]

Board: 2 copper layers, 50.0 x 50.0 mm, 33 parts (0 on the bottom side), 75 nets.

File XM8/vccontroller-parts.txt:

Partlist

Exported from voice-card-controller-1_1.sch at 09.04.2016 21:07:20

EAGLE Version 7.2.0 Copyright (c) 1988-2014 CadSoft

Assembly variant: 

Part       Value                Device               Package         Library           Sheet

C1         100nF                C-EUC0603            C0603           resistor          1
C2         12pF                 C-EUC0603            C0603           resistor          1
C3         12pF                 C-EUC0603            C0603           resistor          1
C4         22uF 25V             CPOL-EUE2.5-5        E2,5-5          resistor          1
C5         10uF                 C-EUC0805            C0805           resistor          1
C7         100nF                C-EUC0603            C0603           resistor          1
C8         100nF                C-EUC0603            C0603           resistor          1
C9         100nF                C-EUC0603            C0603           resistor          1
C10        100nF                C-EUC0603            C0603           resistor          1
C11        100nF                C-EUC0603            C0603           resistor          1
C12        100nF                C-EUC0603            C0603           resistor          1
C13        100nF                C-EUC0603            C0603           resistor          1
D1                              DIODE-SOD80C         SOD80C          diode             1
D2                              DIODE-SOD80C         SOD80C          diode             1
DAC-ADR                         MA08-2J              MA08-2J         joakim            1
DAC-CTRL                        MA05-2J              MA05-2J         joakim            1
DIG-IN                          MA04-2J              MA04-2J         joakim            1
DIG-OUT                         MA05-2J              MA05-2J         joakim            1
ICP                             MA05-1               MA05-1          joakim            1
INTERRUPTS                      MA04-2J              MA04-2J         joakim            1
JP1                             JP1E                 JP1             jumper            1
MIDI       22-23-2051           22-23-2051           22-23-2051      con-molex         1
OK1        6N137J               6N137J               DIL08-J         joakim            1
POWER      22-23-2021           22-23-2021           22-23-2021      con-molex         1
Q1         8MHz                 XTAL-J               CTS406J         joakim            1
R1         10k                  R-US_R0805           R0805           resistor          1
R2         10R                  R-EU_0207/7          0207/7          resistor          1
R3         220R                 R-US_R0805           R0805           resistor          1
R10        220R                 R-US_R0805           R0805           resistor          1
SPI-IN                          MA04-2J              MA04-2J         joakim            1
SPI-OUT                         MA05-2J              MA05-2J         joakim            1
SPI-OUT-VC                      MA04-2J              MA04-2J         joakim            1
U$1        PIC32MX795F512L-X_PF PIC32MX795F512L-X_PF TQFP100_14X14MC pic32mx-795F-512L 1
